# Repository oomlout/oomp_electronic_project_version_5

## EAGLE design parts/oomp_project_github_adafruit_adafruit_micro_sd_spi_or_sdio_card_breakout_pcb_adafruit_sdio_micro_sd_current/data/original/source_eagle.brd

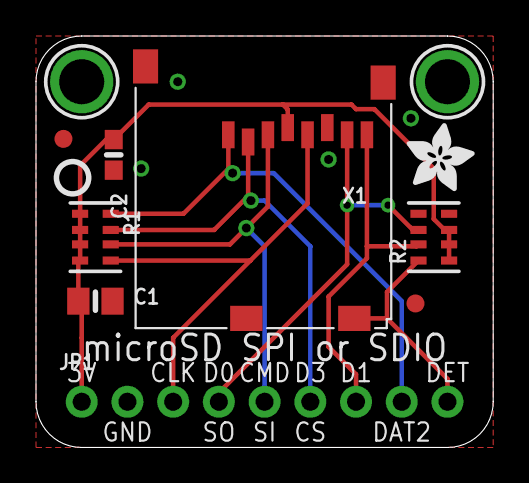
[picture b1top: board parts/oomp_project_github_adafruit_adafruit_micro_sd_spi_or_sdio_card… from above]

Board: 2 copper layers, 25.4 x 22.9 mm, 12 parts (0 on the bottom side), 9 nets.

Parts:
C1: 10uF; 0805-NO
C2: 0.1uF; 0603-NO
FID1, FID2: FIDUCIAL""; FIDUCIAL_1MM
JP1: 1X09_ROUND_70
R1, R2: 47K; RESPACK_4X0603
U$1, U$2: MOUNTINGHOLE2.5; MOUNTINGHOLE_2.5_PLATED
U$4: ADAFRUIT_3.5MM
U$7: PCBFEAT-REV-040
X1: microSD; MICROSD

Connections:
3.3V: C1.1, C2.1, JP1.1, R1.1, R1.2, R1.3, R1.4, R2.1, R2.2, R2.3, X1.4
CARDDET: JP1.9, R2.8, X1.CD1
CS: JP1.6, R1.7, X1.2
DAT1: JP1.7, R2.7, X1.8
DAT2: JP1.8, R1.8, X1.1
DI: JP1.5, R1.6, X1.3
DO: JP1.4, R2.6, X1.7
GND: C1.2, C2.2, JP1.2, X1.6, X1.MT1, X1.MT2
SCLK: JP1.3, R1.5, X1.5

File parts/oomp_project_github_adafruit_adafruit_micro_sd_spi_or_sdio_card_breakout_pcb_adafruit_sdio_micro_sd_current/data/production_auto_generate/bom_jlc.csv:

Comment,Designator,Footprint,LCSC Part #
,JP1,Adafruit SDIO microSD-import-fps:1X09_ROUND_70,C2932701
,U$4,Adafruit SDIO microSD-import-fps:ADAFRUIT_3.5MM,
,U$7,Adafruit SDIO microSD-import-fps:PCBFEAT-REV-040,
0.1uF,C2,Adafruit SDIO microSD-import-fps:0603-NO,C14663
10uF,C1,Adafruit SDIO microSD-import-fps:0805-NO,
47K,"R1,R2",Adafruit SDIO microSD-import-fps:RESPACK_4X0603,C2907042
microSD,X1,Adafruit SDIO microSD-import-fps:MICROSD,

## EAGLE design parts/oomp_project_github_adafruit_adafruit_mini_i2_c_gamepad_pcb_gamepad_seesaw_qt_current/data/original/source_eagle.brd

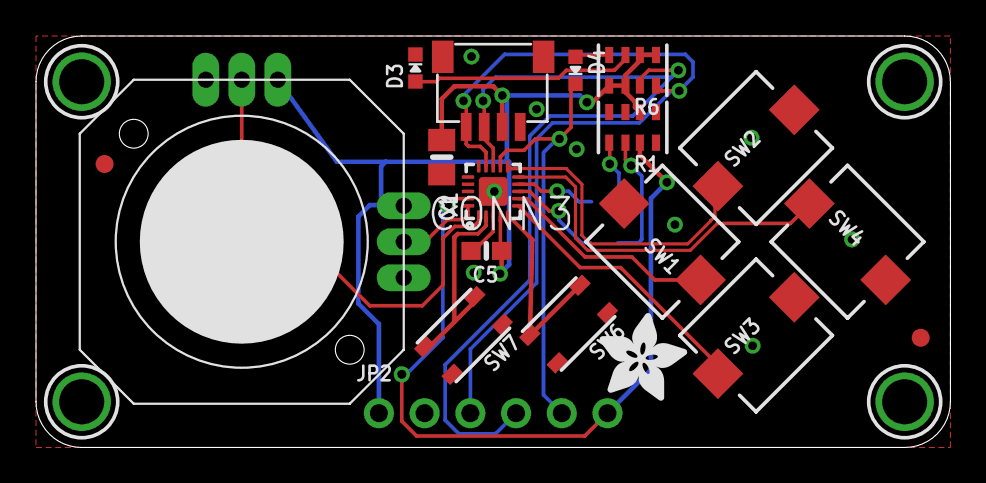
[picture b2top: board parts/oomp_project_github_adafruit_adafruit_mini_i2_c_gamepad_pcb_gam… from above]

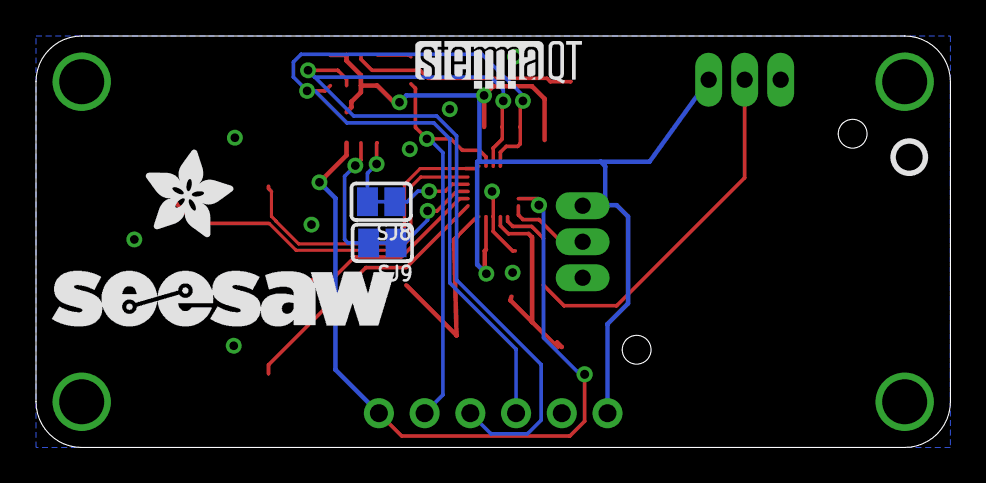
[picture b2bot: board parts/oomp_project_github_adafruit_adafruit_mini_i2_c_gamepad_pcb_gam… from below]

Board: 2 copper layers, 50.8 x 22.9 mm, 47 parts (16 on the bottom side), 20 nets.

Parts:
C1: 10uF; 0805-NO
C5: 0.1uF; 0603-NO
CONN3: STEMMA_I2C_QT; JST_SH4
D3: GREEN; CHIPLED_0603_NOOUTLINE
D4: Red; CHIPLED_0603_NOOUTLINE
FID1, FID2: FIDUCIAL_1MM
JOY2: JOYSTICK_ANALOG_XY; JOYSTICK_ANALOG_MINITHM
JP2: 1X06_ROUND
PLABEL0: PLABEL0
PLABEL1: PLABEL1
PLABEL2: PLABEL2
PLABEL3: PLABEL3
PLABEL4: PLABEL4
PLABEL5: PLABEL5
PLABEL6: PLABEL6
PLABEL7: PLABEL7
PLABEL8: PLABEL8
PLABEL9: PLABEL9
PLABEL10: PLABEL10
PLABEL11: PLABEL11
PLABEL12: PLABEL12
PLABEL13: PLABEL13
PLABEL14: PLABEL14
PLABEL15: PLABEL15
PLABEL16: PLABEL16
PLABEL17: PLABEL17
R1, R6: 10K Pack; RESPACK_4X0603
SJ8, SJ9: SOLDERJUMPER_CLOSEDWIRE
SW1, SW2, SW3, SW4: SJ_BUTTON; PUSHBUTTON_SMD_SJ
SW6, SW7: KMR2; BTN_RKB2_4.6X2.8
U$1, U$2, U$3, U$4: MOUNTINGHOLE2.5; MOUNTINGHOLE_2.5_PLATED
U$5: STEMMAQT
U$7: PCBFEAT-REV-040
U$9, U$11: ADAFRUIT_5MM
U$12: SEESAW_LOGO
X1: ATTINY8X6_QFN; QFN20_3MM

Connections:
ADDR0: SJ9.1, X1.8
ADDR1: SJ8.1, X1.9
BUTT_A: SW4.P$2, X1.10
BUTT_B: SW3.P$2, X1.6
BUTT_SEL: SW6.B, SW6.B', X1.5
BUTT_START: SW7.B, SW7.B', X1.2
BUTT_X: SW2.P$2, X1.11
BUTT_Y: SW1.P$2, X1.7
GND: C1.2, C5.2, CONN3.1, CONN3.MT1, CONN3.MT2, D3.C, JOY2.X-, JOY2.Y-, JP2.2, R1.1, R1.3, R1.4, R1.8, SW1.P$1, SW2.P$1, SW3.P$1, SW4.P$1, SW6.A, SW6.A', SW7.A, SW7.A', X1.3, X1.PAD
IRQ: D4.C, JP2.5, X1.12
JOY_X: JOY2.X, X1.1
JOY_Y: JOY2.Y, X1.20
unnamed: D3.A, R6.3
unnamed: R1.6, SJ9.2
unnamed: R1.5, SJ8.2
unnamed: D4.A, R6.4
SCL: CONN3.4, JP2.3, R6.8, X1.14
SDA: CONN3.3, JP2.4, R6.7, X1.13
UPDI: JP2.6, R1.7, X1.19
VCC: C1.1, C5.1, CONN3.2, JOY2.X+, JOY2.Y+, JP2.1, R1.2, R6.1, R6.2, R6.5, R6.6, X1.4

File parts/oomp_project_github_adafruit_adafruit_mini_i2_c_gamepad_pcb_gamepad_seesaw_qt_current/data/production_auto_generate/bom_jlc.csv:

Comment,Designator,Footprint,LCSC Part #
,JP2,Gamepad Seesaw QT rev A-import-fps:1X06_ROUND,C37208
,"U$9,U$11",Gamepad Seesaw QT rev A-import-fps:ADAFRUIT_5MM,
,U$7,Gamepad Seesaw QT rev A-import-fps:PCBFEAT-REV-040,
,PLABEL0,Gamepad Seesaw QT rev A-import-fps:PLABEL0,
,PLABEL1,Gamepad Seesaw QT rev A-import-fps:PLABEL1,
,PLABEL10,Gamepad Seesaw QT rev A-import-fps:PLABEL10,
,PLABEL11,Gamepad Seesaw QT rev A-import-fps:PLABEL11,
,PLABEL12,Gamepad Seesaw QT rev A-import-fps:PLABEL12,
,PLABEL13,Gamepad Seesaw QT rev A-import-fps:PLABEL13,
,PLABEL14,Gamepad Seesaw QT rev A-import-fps:PLABEL14,
,PLABEL15,Gamepad Seesaw QT rev A-import-fps:PLABEL15,
,PLABEL16,Gamepad Seesaw QT rev A-import-fps:PLABEL16,
,PLABEL17,Gamepad Seesaw QT rev A-import-fps:PLABEL17,
,PLABEL2,Gamepad Seesaw QT rev A-import-fps:PLABEL2,
,PLABEL3,Gamepad Seesaw QT rev A-import-fps:PLABEL3,
,PLABEL4,Gamepad Seesaw QT rev A-import-fps:PLABEL4,
,PLABEL5,Gamepad Seesaw QT rev A-import-fps:PLABEL5,
,PLABEL6,Gamepad Seesaw QT rev A-import-fps:PLABEL6,
,PLABEL7,Gamepad Seesaw QT rev A-import-fps:PLABEL7,
,PLABEL8,Gamepad Seesaw QT rev A-import-fps:PLABEL8,
,PLABEL9,Gamepad Seesaw QT rev A-import-fps:PLABEL9,
,U$12,Gamepad Seesaw QT rev A-import-fps:SEESAW_LOGO,
,U$5,Gamepad Seesaw QT rev A-import-fps:STEMMAQT,
0.1uF,C5,Gamepad Seesaw QT rev A-import-fps:0603-NO,C14663
10K Pack,"R1,R6",Gamepad Seesaw QT rev A-import-fps:RESPACK_4X0603,C98220
10uF,C1,Gamepad Seesaw QT rev A-import-fps:0805-NO,
ATTINY8X6_QFN,X1,Gamepad Seesaw QT rev A-import-fps:QFN20_3MM,
GREEN,D3,Gamepad Seesaw QT rev A-import-fps:CHIPLED_0603_NOOUTLINE,
JOYSTICK_ANALOG_XY,JOY2,Gamepad Seesaw QT rev A-import-fps:JOYSTICK_ANALOG_MINITHM,
KMR2,"SW6,SW7",Gamepad Seesaw QT rev A-import-fps:BTN_RKB2_4.6X2.8,
Red,D4,Gamepad Seesaw QT rev A-import-fps:CHIPLED_0603_NOOUTLINE,
SJ_BUTTON,"SW1,SW2,SW3,SW4",Gamepad Seesaw QT rev A-import-fps:PUSHBUTTON_SMD_SJ,
STEMMA_I2C_QT,CONN3,Gamepad Seesaw QT rev A-import-fps:JST_SH4,C160404

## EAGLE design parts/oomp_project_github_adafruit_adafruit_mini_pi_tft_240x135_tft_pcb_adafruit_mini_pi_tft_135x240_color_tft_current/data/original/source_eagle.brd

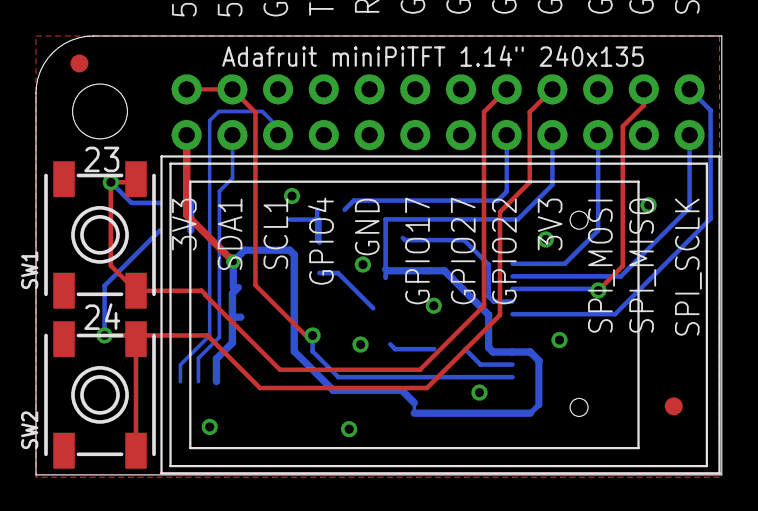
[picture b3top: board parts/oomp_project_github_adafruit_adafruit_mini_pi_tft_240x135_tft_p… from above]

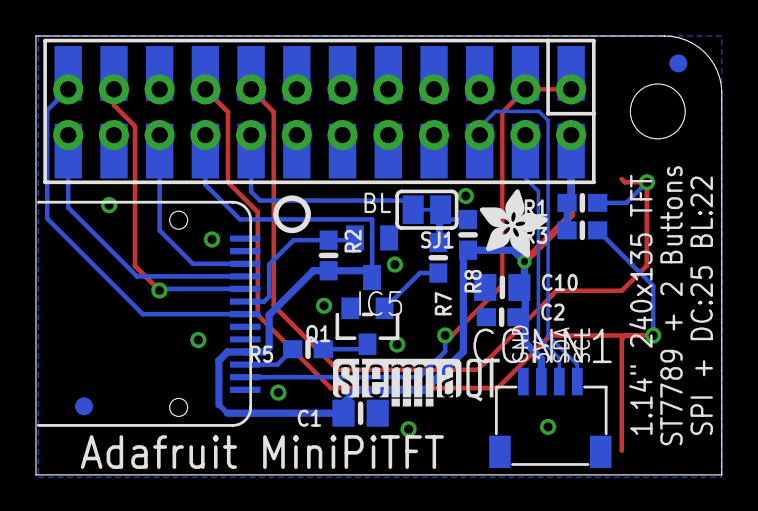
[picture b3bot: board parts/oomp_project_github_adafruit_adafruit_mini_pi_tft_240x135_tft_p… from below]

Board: 2 copper layers, 38.1 x 24.4 mm, 24 parts (18 on the bottom side), 17 nets.

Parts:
C1, C10: 10uF; 0805-NO
C2: 1uF; 0603-NO
CONN1: STEMMA_I2C_QT; JST_SH4
DISP1: DISP_LCD_GENERIC_SPI_1.14IN_13P; TFT_1.14IN_240X135_WRAPAROUND
FID1, FID2, FID3, FID4: FIDUCIAL_1MM
IC5: APX803; SOT23
Q1: MMBT2222; SOT23-WIDE
R1, R2, R3, R8: 10K; 0603-NO
R5: 22; 0603-NO
R7: 1K; 0603-NO
RASPI1: RASPBERRYPI_2X12_THMSMT
SJ1: SOLDERJUMPER_CLOSEDWIRE
SW1, SW2: EVQ-Q2_SMALLER
U$4: MICROSD; ADAFRUIT_3.5MM
U$6: PCBFEAT-REV-040
U$15: STEMMAQT

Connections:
3.3V: C1.2, C2.2, C10.2, CONN1.2, DISP1.10, IC5.3, R1.2, R2.2, R3.2, R8.2, RASPI1.1, RASPI1.17
5.0V: DISP1.12, RASPI1.2, RASPI1.4
BACKLIGHT: R7.1, R8.1, SJ1.1
BUTTONA: R1.1, RASPI1.16, SW1.A, SW1.A'
BUTTONB: R3.1, RASPI1.18, SW2.A, SW2.A'
GND: C1.1, C2.1, C10.1, CONN1.1, DISP1.8, DISP1.13, IC5.1, Q1.2, RASPI1.6, RASPI1.9, RASPI1.14, RASPI1.20, SW1.B, SW1.B', SW2.B, SW2.B'
GPIO22: RASPI1.15, SJ1.2
LED_K: DISP1.11, R5.2
MOSI: DISP1.3, RASPI1.19
unnamed: Q1.1, R7.2
unnamed: Q1.3, R5.1
SCL: CONN1.4, RASPI1.5
SCLK: DISP1.4, RASPI1.23
SDA: CONN1.3, RASPI1.3
TFT_CS: DISP1.7, RASPI1.24
TFT_DC: DISP1.5, RASPI1.22
TFT_RST: DISP1.6, IC5.2, R2.1

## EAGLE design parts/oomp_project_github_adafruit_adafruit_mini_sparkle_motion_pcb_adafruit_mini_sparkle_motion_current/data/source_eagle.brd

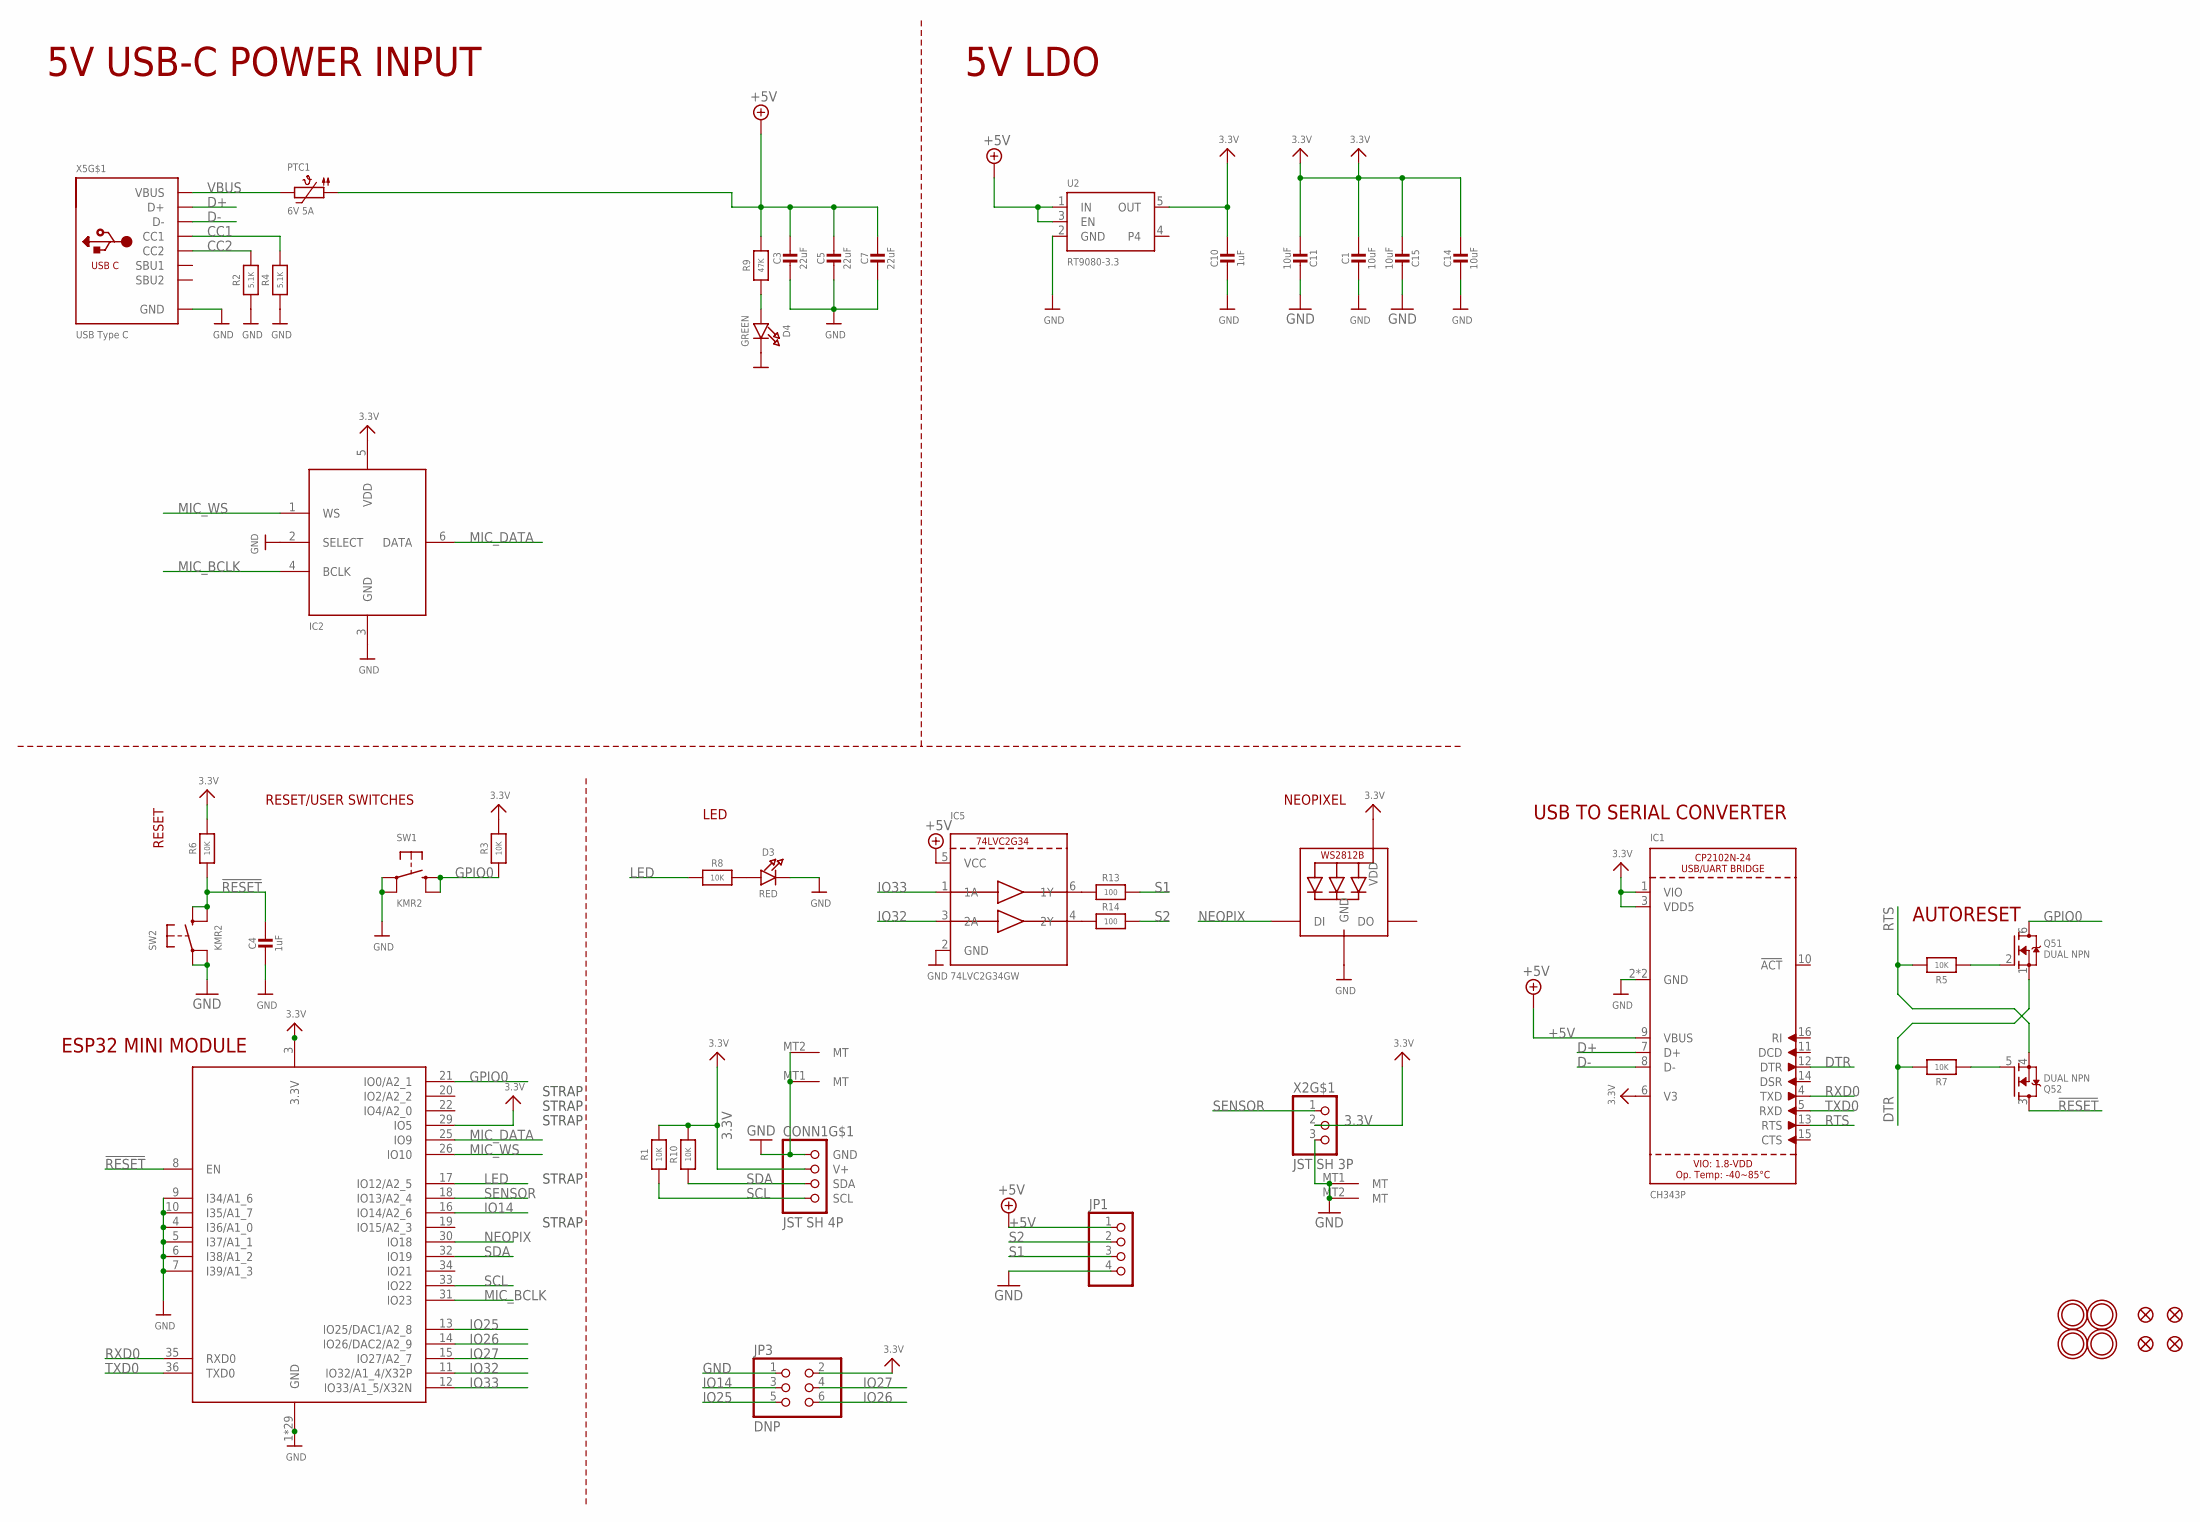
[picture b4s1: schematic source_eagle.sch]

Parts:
C1, C11, C14, C15: 10uF; 0805-NO
C3, C5, C7: 22uF; 0805-NO
C4, C10: 1uF; _0402NO
CONN1: JST SH 4P; JST_SH4
D3: RED; CHIPLED_0603_NOOUTLINE
D4: GREEN; CHIPLED_0603_NOOUTLINE
IC1: CH343P; QFN16_3MM
IC2: ICS-43434; SPH0645LM4H
IC5: 74LVC2G34GW; SC70-6L
JP1: HEADER-1X4; 1X04_OVAL
JP3: DNP; 2X03_ROUND_70MIL
LED1: WS2812B_SK6805_1515; SK6805_1515
PTC1: 6V 5A; PTC1210
Q5: DUAL NPN; SOT363; JLC_ROTATION 90
R1, R3, R5, R6, R7, R8, R10: 10K; _0402NO
R2, R4: 5.1K; _0402NO
R9: 47K; _0402NO
R13, R14: 100; _0402NO
SW1, SW2: KMR2; BTN_RKB2_4.6X2.8
U2: RT9080-3.3; SOT23-5; JLC_ROTATION 0
U$14, U$20, U$28, U$31: MOUNTINGHOLE2.5; MOUNTINGHOLE_2.5_PLATED
U$23, U$25, U$34, U$35: FIDUCIAL_0.5MM
X2: JST SH 3P; JST_SH3
X4: ESP32-MINI-1
X5: USB Type C; USB_C_CUSB31-CFM2AX-01-X

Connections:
3.3V: C1.1, C10.1, C11.1, C14.1, C15.1, CONN1.2 (V+), IC1.1 (VIO), IC1.3 (VDD5), IC1.6 (V3), IC2.5 (VDD), JP3.2, LED1.2 (VDD), R1.2, R3.2, R6.2, R10.2, U2.5 (OUT), X2.2, X4.3 (3.3V), X4.29 (IO5)
!RESET: C4.1, Q5.3 (D), R6.1, SW2.B (S), SW2.B' (S1), X4.8 (EN)
+5V: C3.1, C5.1, C7.1, IC1.9 (VBUS), IC5.5 (VCC), JP1.1, PTC1.P$1 (1), R9.2, U2.1 (IN), U2.3 (EN)
CC1: R4.2, X5.A5 (CC1)
CC2: R2.2, X5.B5 (CC2)
D+: IC1.7 (D+), X5.A6 (D+), X5.B6 (D+)
D-: IC1.8 (D-), X5.A7 (D-), X5.B7 (D-)
DTR: IC1.12 (DTR), Q5.1 (S), R7.2
GND: C1.2, C3.2, C4.2, C5.2, C7.2, C10.2, C11.2, C14.2, C15.2, CONN1.1 (GND), CONN1.MT1 (MT), CONN1.MT2 (MT), D3.C, D4.C, IC1.2 (GND), IC1.THERMAL (GND), IC2.2 (SELECT), IC2.3 (GND), IC5.2 (GND), JP1.4, JP3.1, LED1.4 (GND), R2.1, R4.1, SW1.A, SW1.A' (P1), SW2.A, SW2.A' (P1), U2.2 (GND), X2.3, X2.MT1 (MT), X2.MT2 (MT), X4.1 (GND), X4.2 (GND), X4.4 (I36/A1_0), X4.5 (I37/A1_1), X4.6 (I38/A1_2), X4.7 (I39/A1_3), X4.9 (I34/A1_6), X4.10 (I35/A1_7), X4.27 (GND), X4.38 (GND), X4.39 (GND), X4.40 (GND), X4.41 (GND), X4.42 (GND), X4.43 (GND), X4.44 (GND), X4.45 (GND), X4.46 (GND), X4.47 (GND), X4.48 (GND), X4.49 (GND), X4.50 (GND), X4.51 (GND), X4.52 (GND), X4.53 (GND), X4.54 (GND), X4.55 (GND), X4.56 (GND), X4.57 (GND), X4.58 (GND), X4.59 (GND), X4.60 (GND), X4.61 (GND), X4.62 (GND), X4.63 (GND), X5.A1B12 (GND), X5.B1A12 (GND)
GPIO0: Q5.6 (D), R3.1, SW1.B (S), SW1.B' (S1), X4.21 (IO0/A2_1)
IO14: JP3.3, X4.16 (IO14/A2_6)
IO25: JP3.5, X4.13 (IO25/DAC1/A2_8)
IO26: JP3.6, X4.14 (IO26/DAC2/A2_9)
IO27: JP3.4, X4.15 (IO27/A2_7)
IO32: IC5.3 (2A), X4.11 (IO32/A1_4/X32P)
IO33: IC5.1 (1A), X4.12 (IO33/A1_5/X32N)
LED: R8.1, X4.17 (IO12/A2_5)
MIC_BCLK: IC2.4 (BCLK), X4.31 (IO23)
MIC_DATA: IC2.6 (DATA), X4.25 (IO9)
MIC_WS: IC2.1 (WS), X4.26 (IO10)
unnamed: D3.A, R8.2
unnamed: Q5.5 (G), R7.1
unnamed: Q5.2 (G), R5.1
unnamed: IC5.6 (1Y), R13.1
unnamed: IC5.4 (2Y), R14.1
unnamed: D4.A, R9.1
NEOPIX: LED1.1 (DI), X4.30 (IO18)
RTS: IC1.13 (RTS), Q5.4 (S), R5.2
RXD0: IC1.4 (TXD), X4.35 (RXD0)
S1: JP1.3, R13.2
S2: JP1.2, R14.2
SCL: CONN1.4 (SCL), R1.1, X4.33 (IO22)
SDA: CONN1.3 (SDA), R10.1, X4.32 (IO19)
SENSOR: X2.1, X4.18 (IO13/A2_4)
TXD0: IC1.5 (RXD), X4.36 (TXD0)
VBUS: PTC1.P$2 (2), X5.A4B9 (VBUS), X5.B4A9 (VBUS)

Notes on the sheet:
5V USB-C POWER INPUT
RESET
LED
NEOPIXEL
ESP32 MINI MODULE
RESET/USER SWITCHES
AUTORESET
USB TO SERIAL CONVERTER
5V LDO
STRAP

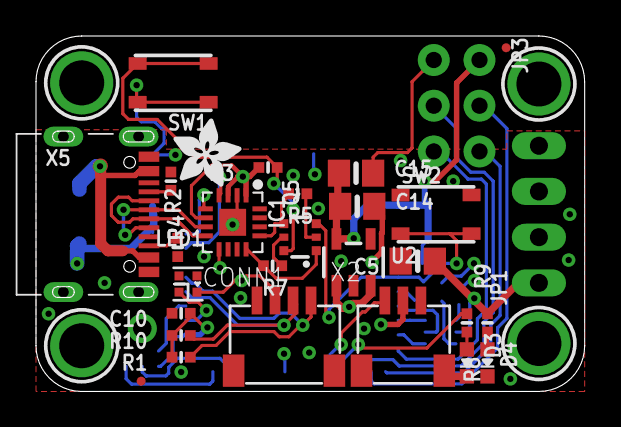
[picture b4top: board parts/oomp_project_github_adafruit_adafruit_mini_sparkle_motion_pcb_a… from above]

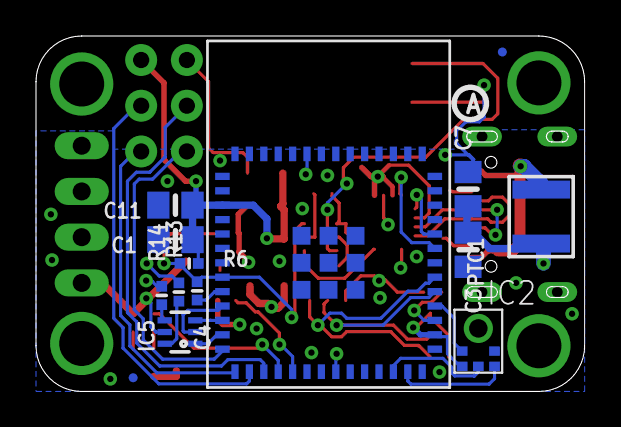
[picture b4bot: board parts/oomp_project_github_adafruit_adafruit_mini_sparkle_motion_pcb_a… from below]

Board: 4 copper layers, 30.5 x 19.7 mm, 68 parts (22 on the bottom side), 36 nets.

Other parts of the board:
PLABEL0: PLABEL0
PLABEL1: PLABEL1
PLABEL2: PLABEL2
PLABEL3: PLABEL3
PLABEL4: PLABEL4
PLABEL5: PLABEL5
PLABEL6: PLABEL6
PLABEL7: PLABEL7
PLABEL8: PLABEL8
PLABEL9: PLABEL9
PLABEL10: PLABEL10
PLABEL11: PLABEL11
PLABEL15: PLABEL15
PLABEL16: PLABEL16
PLABEL17: PLABEL17
PLABEL18: PLABEL18
PLABEL20: PLABEL20
PLABEL21: PLABEL21
PLABEL22: PLABEL22
PLABEL23: PLABEL23
U$27: ADAFRUIT_3.5MM
U$29: PCBFEAT-REV-040

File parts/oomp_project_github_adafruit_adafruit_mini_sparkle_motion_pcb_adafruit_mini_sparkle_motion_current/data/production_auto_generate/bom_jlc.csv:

Comment,Designator,Footprint,LCSC Part #
,JP1,Adafruit Mini Sparkle Motion-import-fps:1X04_OVAL,C42431795
,U$27,Adafruit Mini Sparkle Motion-import-fps:ADAFRUIT_3.5MM,
,U$29,Adafruit Mini Sparkle Motion-import-fps:PCBFEAT-REV-040,
,PLABEL0,Adafruit Mini Sparkle Motion-import-fps:PLABEL0,
,PLABEL1,Adafruit Mini Sparkle Motion-import-fps:PLABEL1,
,PLABEL10,Adafruit Mini Sparkle Motion-import-fps:PLABEL10,
,PLABEL11,Adafruit Mini Sparkle Motion-import-fps:PLABEL11,
,PLABEL15,Adafruit Mini Sparkle Motion-import-fps:PLABEL15,
,PLABEL16,Adafruit Mini Sparkle Motion-import-fps:PLABEL16,
,PLABEL17,Adafruit Mini Sparkle Motion-import-fps:PLABEL17,
,PLABEL18,Adafruit Mini Sparkle Motion-import-fps:PLABEL18,
,PLABEL2,Adafruit Mini Sparkle Motion-import-fps:PLABEL2,
,PLABEL20,Adafruit Mini Sparkle Motion-import-fps:PLABEL20,
,PLABEL21,Adafruit Mini Sparkle Motion-import-fps:PLABEL21,
,PLABEL22,Adafruit Mini Sparkle Motion-import-fps:PLABEL22,
,PLABEL23,Adafruit Mini Sparkle Motion-import-fps:PLABEL23,
,PLABEL3,Adafruit Mini Sparkle Motion-import-fps:PLABEL3,
,PLABEL4,Adafruit Mini Sparkle Motion-import-fps:PLABEL4,
,PLABEL5,Adafruit Mini Sparkle Motion-import-fps:PLABEL5,
,PLABEL6,Adafruit Mini Sparkle Motion-import-fps:PLABEL6,
,PLABEL7,Adafruit Mini Sparkle Motion-import-fps:PLABEL7,
,PLABEL8,Adafruit Mini Sparkle Motion-import-fps:PLABEL8,
,PLABEL9,Adafruit Mini Sparkle Motion-import-fps:PLABEL9,
100,"R13,R14",Adafruit Mini Sparkle Motion-import-fps:_0402NO,C2906860
10K,"R1,R3,R5,R6,R7,R8,R10",Adafruit Mini Sparkle Motion-import-fps:_0402NO,C2906861
10uF,"C1,C11,C14,C15",Adafruit Mini Sparkle Motion-import-fps:0805-NO,
1uF,"C4,C10",Adafruit Mini Sparkle Motion-import-fps:_0402NO,C2887021
22uF,"C3,C5,C7",Adafruit Mini Sparkle Motion-import-fps:0805-NO,
47K,R9,Adafruit Mini Sparkle Motion-import-fps:_0402NO,C25792
5.1K,"R2,R4",Adafruit Mini Sparkle Motion-import-fps:_0402NO,C25905
6V 5A,PTC1,Adafruit Mini Sparkle Motion-import-fps:PTC1210,
74LVC2G34GW,IC5,Adafruit Mini Sparkle Motion-import-fps:SC70-6L,
CH343P,IC1,Adafruit Mini Sparkle Motion-import-fps:QFN16_3MM,
DNP,JP3,Adafruit Mini Sparkle Motion-import-fps:2X03_ROUND_70MIL,
DUAL NPN,Q5,Adafruit Mini Sparkle Motion-import-fps:SOT363,
ESP32-MINI-1,X4,Adafruit Mini Sparkle Motion-import-fps:ESP32-MINI-1,
FIDUCIAL_0.5MM,"U$23,U$25,U$34,U$35",Adafruit Mini Sparkle Motion-import-fps:FIDUCIAL_0.5MM,
GREEN,D4,Adafruit Mini Sparkle Motion-import-fps:CHIPLED_0603_NOOUTLINE,
ICS-43434,IC2,Adafruit Mini Sparkle Motion-import-fps:SPH0645LM4H,
JST SH 3P,X2,Adafruit Mini Sparkle Motion-import-fps:JST_SH3,C265338
JST SH 4P,CONN1,Adafruit Mini Sparkle Motion-import-fps:JST_SH4,C160404
KMR2,"SW1,SW2",Adafruit Mini Sparkle Motion-import-fps:BTN_RKB2_4.6X2.8,
RED,D3,Adafruit Mini Sparkle Motion-import-fps:CHIPLED_0603_NOOUTLINE,
RT9080-3.3,U2,Adafruit Mini Sparkle Motion-import-fps:SOT23-5,
USB Type C,X5,Adafruit Mini Sparkle Motion-import-fps:USB_C_CUSB31-CFM2AX-01-X,
WS2812B_SK6805_1515,LED1,Adafruit Mini Sparkle Motion-import-fps:SK6805_1515,

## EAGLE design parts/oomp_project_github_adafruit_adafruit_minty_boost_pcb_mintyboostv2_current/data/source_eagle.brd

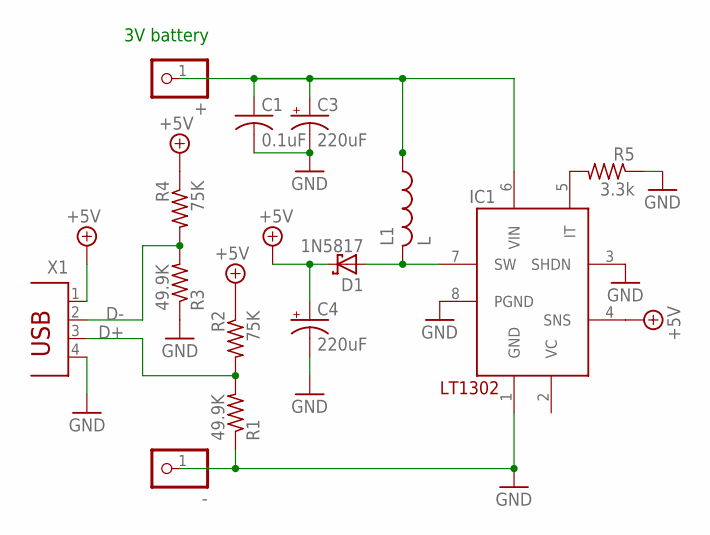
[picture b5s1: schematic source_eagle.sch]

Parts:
+: PINHD-1X1; 1X01
-: PINHD-1X1; 1X01
C1: 0.1uF; C025-025X050
C3, C4: 220uF; E2,5-5
D1: 1N5817; DO41-7
IC1: LT1302; DIL08
L1: L; 6000
R1, R3: 49.9K; 0204/5
R2, R4: 75K; 0204/5
R5: 3.3k; 0204/5
X1: PN87520

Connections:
+5V: C4.+, D1.C, IC1.4 (SNS), R2.1, R4.1, X1.1
BATT+: +.1, C1.1, C3.+, IC1.6 (VIN), L1.1
D+: R1.2, R2.2, X1.3
D-: R3.2, R4.2, X1.2
GND: -.1, C1.2, C3.-, C4.-, IC1.1 (GND), IC1.3 (SHDN), IC1.8 (PGND), R1.1, R3.1, R5.1, X1.4
unnamed: IC1.5 (IT), R5.2
unnamed: D1.A, IC1.7 (SW), L1.2

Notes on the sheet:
3V battery

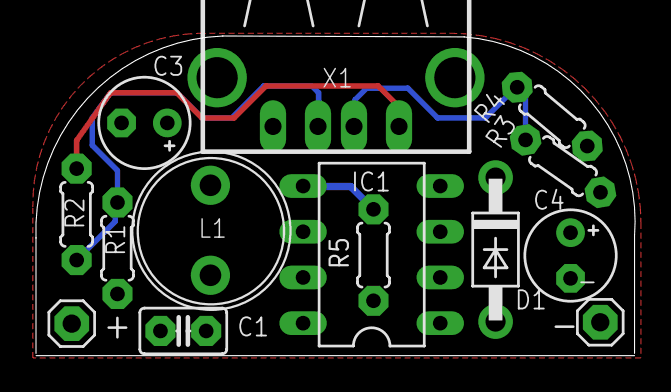
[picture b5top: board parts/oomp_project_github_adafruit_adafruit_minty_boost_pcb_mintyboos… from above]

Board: 2 copper layers, 33.3 x 17.8 mm, 14 parts (0 on the bottom side), 7 nets.

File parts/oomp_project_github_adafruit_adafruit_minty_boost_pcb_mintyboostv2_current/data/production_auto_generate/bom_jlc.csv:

Comment,Designator,Footprint,LCSC Part #
,"+0,-0",mintyboostv2-import-fps:1X01,C7501259
,X1,mintyboostv2-import-fps:PN87520,
0.1uF,C1,mintyboostv2-import-fps:C025-025X050,
1N5817,D1,mintyboostv2-import-fps:DO41-7,
220uF,"C3,C4","mintyboostv2-import-fps:E2,5-5",
3.3k,R5,mintyboostv2-import-fps:0204_5,
49.9K,"R1,R3",mintyboostv2-import-fps:0204_5,
75K,"R2,R4",mintyboostv2-import-fps:0204_5,
L,L1,mintyboostv2-import-fps:6000,
LT1302,IC1,mintyboostv2-import-fps:DIL08,

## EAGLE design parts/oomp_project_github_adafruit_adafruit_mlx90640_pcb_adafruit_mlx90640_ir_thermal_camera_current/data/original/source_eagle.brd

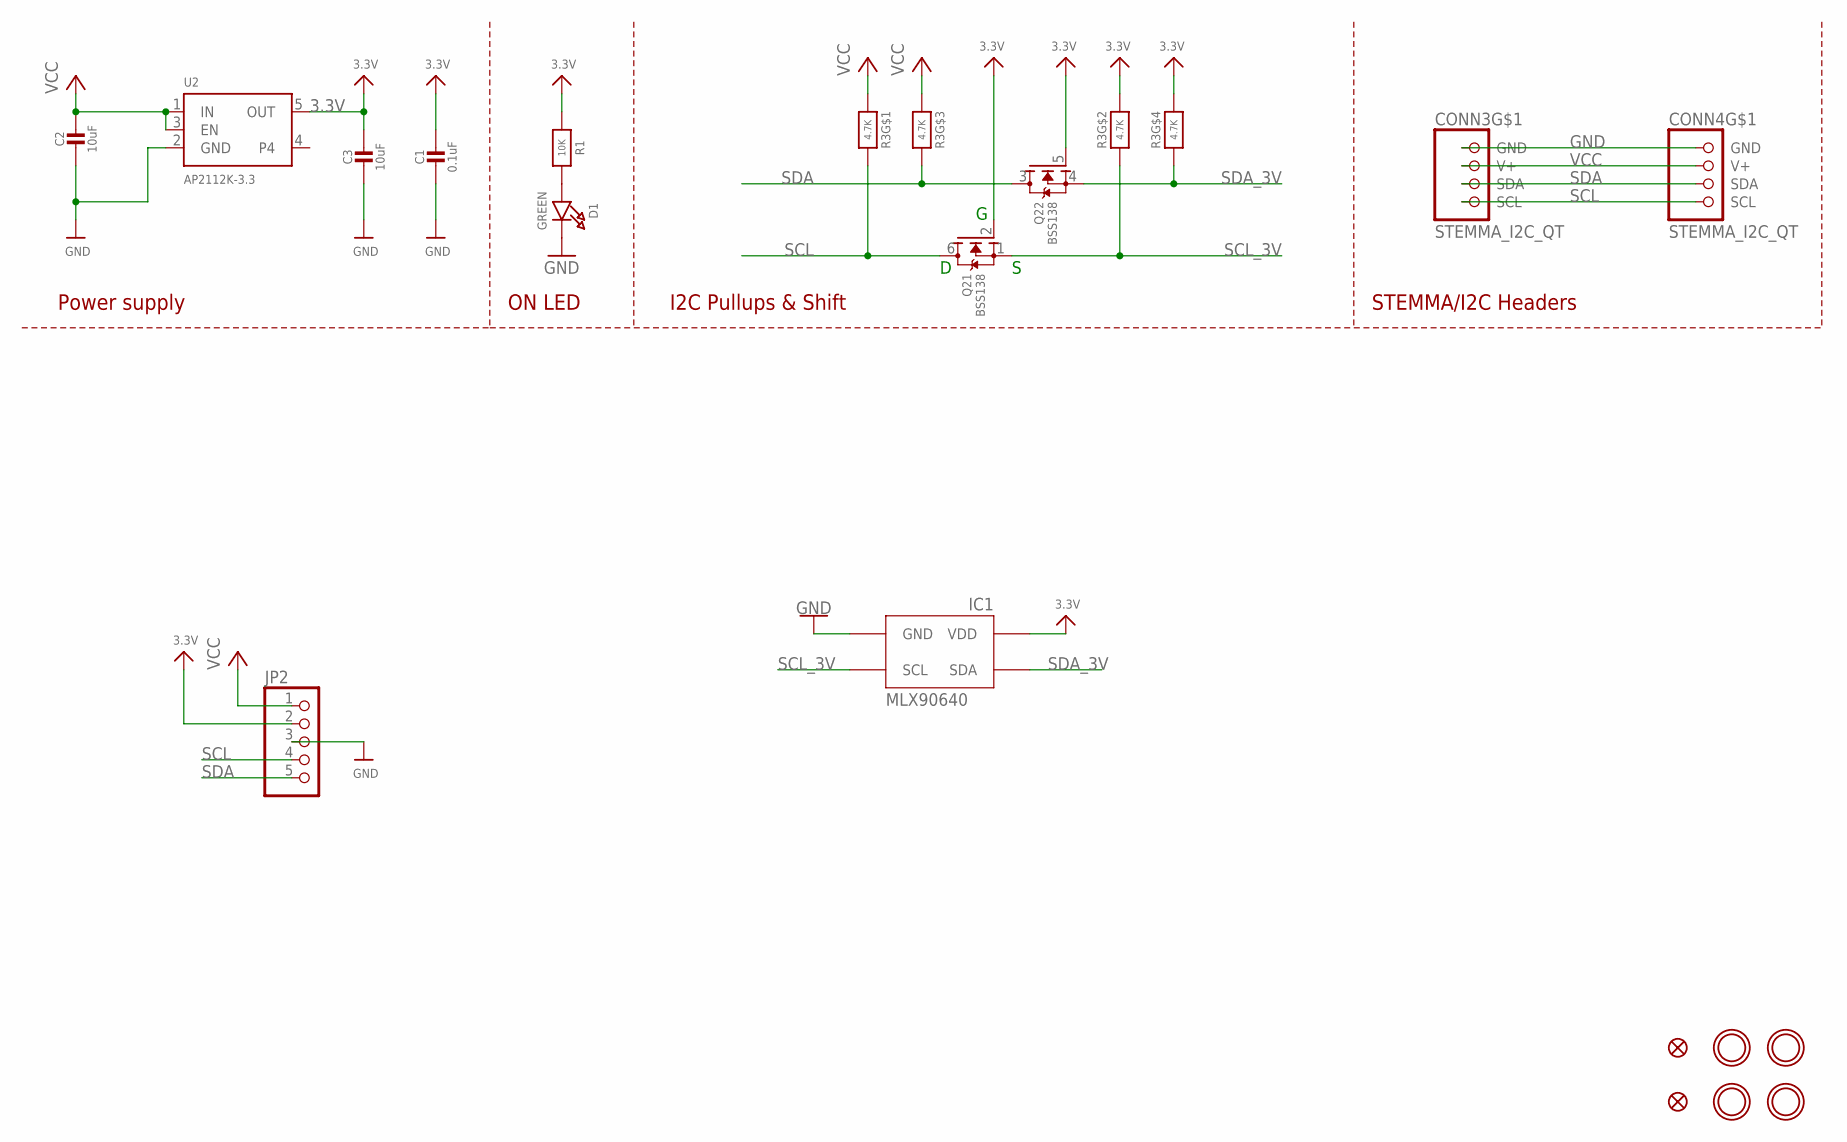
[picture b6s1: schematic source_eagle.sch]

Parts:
C1: 0.1uF; 0603-NO
C2, C3: 10uF; 0805-NO
CONN3, CONN4: STEMMA_I2C_QT; JST_SH4
D1: GREEN; CHIPLED_0603_NOOUTLINE
FID3, FID4: FIDUCIAL_1MM
IC1: MLX90640
JP2: HEADER-1X5ROUND; 1X05_ROUND
Q2: BSS138; SOT363
R1: 10K; 0603-NO
R3: 4.7K; RESPACK_4X0603
U2: AP2112K-3.3; SOT23-5
U$1, U$17, U$19, U$21: MOUNTINGHOLE2.5; MOUNTINGHOLE_2.5_PLATED

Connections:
3.3V: C1.1, C3.1, IC1.VDD, JP2.2, Q2.2 (G), Q2.5 (G), R1.1, R3.2 (1), R3.4 (1), U2.5 (OUT)
GND: C1.2, C2.2, C3.2, CONN3.1 (GND), CONN4.1 (GND), D1.C, IC1.GND, JP2.3, U2.2 (GND)
unnamed: D1.A, R1.2
SCL: CONN3.4 (SCL), CONN4.4 (SCL), JP2.4, Q2.6 (D), R3.8 (2)
SCL_3V: IC1.SCL, Q2.1 (S), R3.7 (2)
SDA: CONN3.3 (SDA), CONN4.3 (SDA), JP2.5, Q2.3 (D), R3.6 (2)
SDA_3V: IC1.SDA, Q2.4 (S), R3.5 (2)
VCC: C2.1, CONN3.2 (V+), CONN4.2 (V+), JP2.1, R3.1, R3.3 (1), U2.1 (IN), U2.3 (EN)

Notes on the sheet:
I2C Pullups & Shift
STEMMA/I2C Headers
ON LED
Power supply

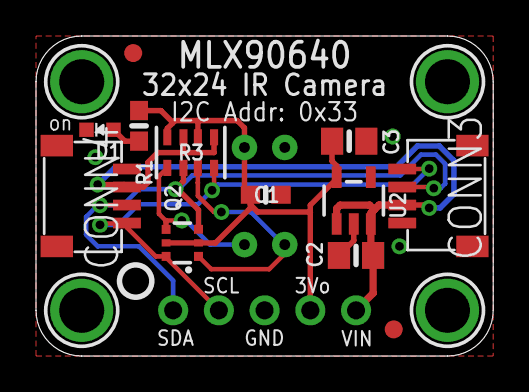
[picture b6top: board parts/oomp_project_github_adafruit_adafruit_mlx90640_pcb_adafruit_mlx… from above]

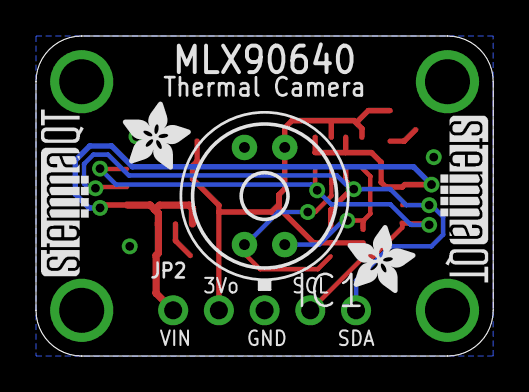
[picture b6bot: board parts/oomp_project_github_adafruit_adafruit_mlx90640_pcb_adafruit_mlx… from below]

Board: 2 copper layers, 25.4 x 17.8 mm, 23 parts (6 on the bottom side), 8 nets.

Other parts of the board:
U$4, U$22: ADAFRUIT_3.5MM
U$25: PCBFEAT-REV-040
U$30, U$31: STEMMAQT

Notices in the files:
parts and their libraries:
microbuilder: This work is placed in the public domain, and may be freely used for commercial and non-commercial work with the following conditions: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
SparkFun-PowerSymbols: Licensing: Creative Commons ShareAlike 4.0 International - https://creativecommons.org/licenses/by-sa/4.0
